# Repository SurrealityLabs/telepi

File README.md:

# telepi
A Raspberry Pi-based teletype, for no real useful purpose

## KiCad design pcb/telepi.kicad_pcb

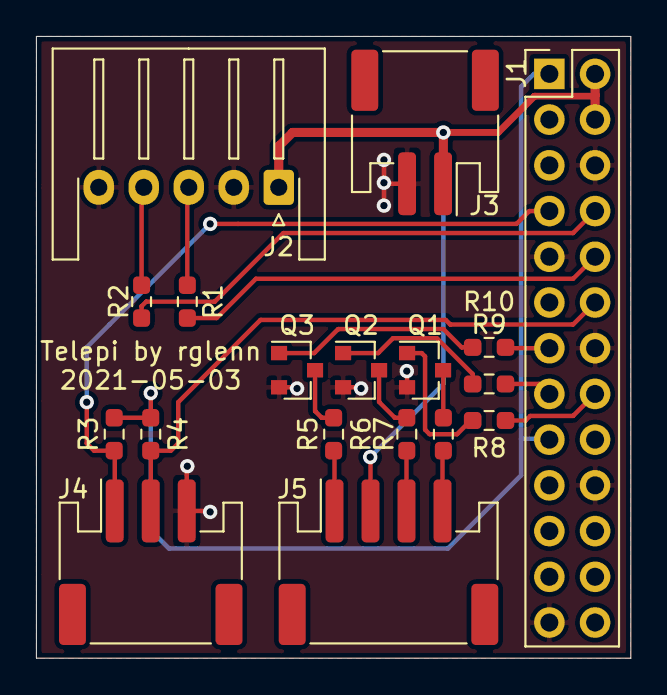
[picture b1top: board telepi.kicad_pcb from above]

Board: 2 copper layers, 33.0 x 34.5 mm, 18 parts (0 on the bottom side), 21 nets.

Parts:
J1: Conn_02x13_Odd_Even; PinHeader_2x13_P2.54mm_Vertical
J2: Conn_01x05; JST_XH_S5B-XH-A-1_1x05_P2.50mm_Horizontal
J3: Conn_01x02; JST_PH_S2B-PH-SM4-TB_1x02-1MP_P2.00mm_Horizontal
J4: Conn_01x03; JST_PH_S3B-PH-SM4-TB_1x03-1MP_P2.00mm_Horizontal
J5: Conn_01x04; JST_PH_S4B-PH-SM4-TB_1x04-1MP_P2.00mm_Horizontal
Q1, Q2, Q3: MMBT3904; SOT-23
R1, R2, R5, R6, R7, R8, R9, R10: 1K; R_0603_1608Metric_Pad0.98x0.95mm_HandSolder
R3, R4: 10K; R_0603_1608Metric_Pad0.98x0.95mm_HandSolder

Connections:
+3V3: J1.1, J1.17, R3.2, R4.2
+5V: J1.2, J1.4, J2.1, J3.1, J5.2
/ACK_BUTTON: J1.7, J4.1, R3.1
/LED_B: J1.16, R8.2
/LED_G: J1.15, R9.2
/LED_R: J1.13, R10.2
/PWR_BUTTON: J1.12, J4.2, R4.1
/RXD: J1.10, R1.2
/TXD: J1.8, R2.2
GND: J1.6, J1.9, J1.14, J1.20, J1.25, J2.2, J2.5, J3.2, J4.3, Q1.2, Q2.2, Q3.2
unnamed: J2.3, R1.1
unnamed: J2.4, R2.1
unnamed: J5.1, R5.1
unnamed: J5.3, R6.1
unnamed: J5.4, R7.1
unnamed: Q1.1, R8.1
unnamed: Q1.3, R7.2
unnamed: Q2.1, R9.1
unnamed: Q2.3, R6.2
unnamed: Q3.1, R10.1
unnamed: Q3.3, R5.2

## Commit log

2021-05-03 Adding PCB
